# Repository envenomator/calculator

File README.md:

# Barebones AVR m328p based programmer's calculator

I was in need of a no-frills, programmer's calculator, not satisfied with the SwissMicros DM16L clone (which uses RPN), I decided to design my own.
This version powers from a USB micro cable, uses the waveshare 2inch 320x240 color display. Complete insanity, but I like it a lot.

The display is mounted to the PCB using two 2mm plastic screws, using a 3d printed shim as standoff.

The calculator with it's back plate glued on, programming port accessible.

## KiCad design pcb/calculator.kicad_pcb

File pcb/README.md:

# Barebones AVR m328p based programmer's calculator

I was in need of a no-frills, programmer's calculator, not satisfied with the SwissMicros DM16L clone (which uses RPN), I decided to design my own.
This version powers from a USB micro cable, uses the waveshare 2inch 320x240 color display. Complete insanity, but I like it a lot.
Code will follow after the PCBs return from the fab.

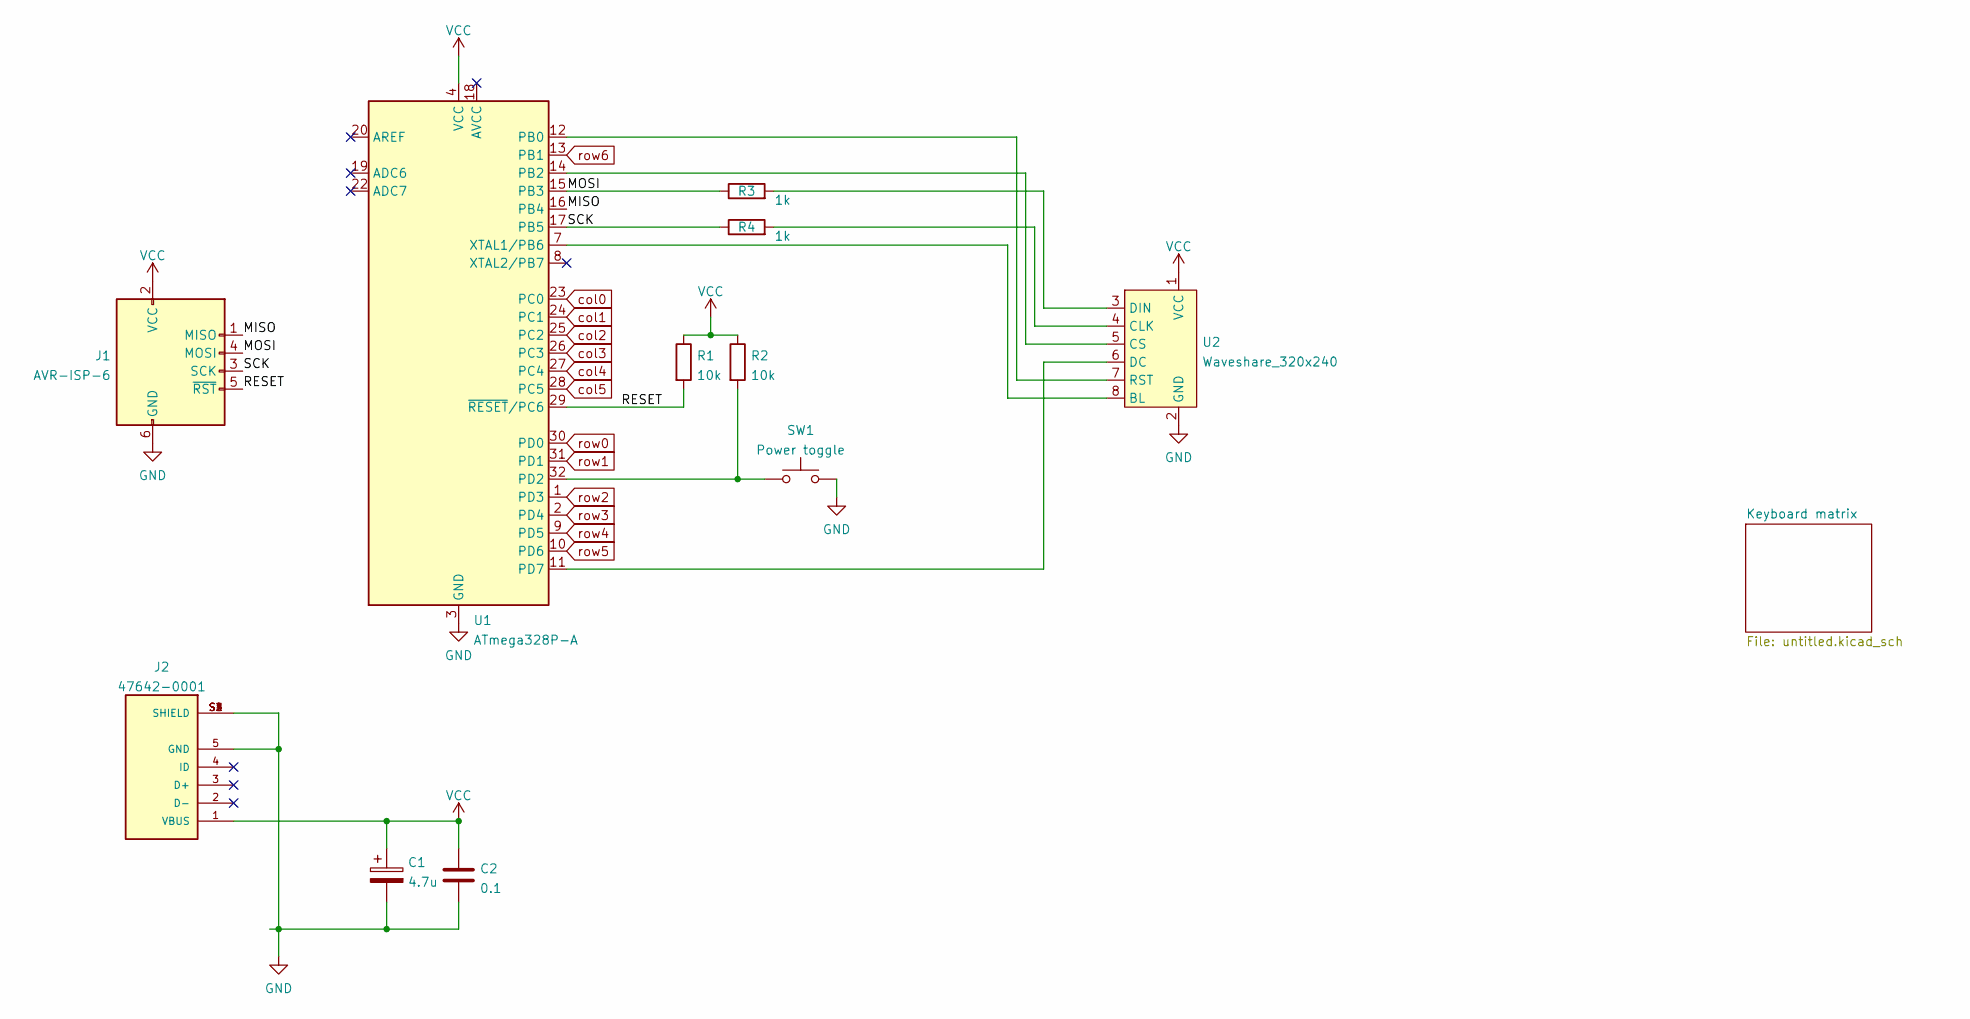
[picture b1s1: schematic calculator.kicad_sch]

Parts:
C1: 4.7u; C_0805_2012Metric_Pad1.18x1.45mm_HandSolder
C2: 0.1; C_0805_2012Metric_Pad1.18x1.45mm_HandSolder
J1: AVR-ISP-6; PinHeader_2x03_P2.54mm_Vertical
J2: 47642-0001; MOLEX_47642-0001
R1, R2: 10k; R_0805_2012Metric_Pad1.20x1.40mm_HandSolder
R3, R4: 1k; R_0805_2012Metric_Pad1.20x1.40mm_HandSolder
SW1: Power toggle; SW_PUSH_6mm
U1: ATmega328P-A; TQFP-32_7x7mm_P0.8mm
U2: Waveshare_320x240

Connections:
/MISO: J1.1 (MISO), U1.16 (PB4)
/MOSI: J1.4 (MOSI), R3.1, U1.15 (PB3)
/RESET: J1.5 (~RST), R1.2, U1.29 (~RESET/PC6)
/SCK: J1.3 (SCK), R4.1, U1.17 (PB5)
GND: C1.2, C2.2, J1.6 (GND), J2.5 (GND), J2.S1 (SHIELD), J2.S2 (SHIELD), J2.S3 (SHIELD), J2.S4 (SHIELD), SW1.2, U1.3 (GND), U1.5 (GND), U1.21 (GND), U2.2 (GND)
unnamed: R2.2, SW1.1, U1.32 (PD2)
unnamed: R3.2, U2.3 (DIN)
unnamed: R4.2, U2.4 (CLK)
unnamed: U1.7 (XTAL1/PB6), U2.8 (BL)
unnamed: U1.11 (PD7), U2.6 (DC)
unnamed: U1.12 (PB0), U2.7 (RST)
unnamed: U1.14 (PB2), U2.5 (CS)
VCC: C1.1, C2.1, J1.2 (VCC), J2.1 (VBUS), R1.1, R2.1, U1.4 (VCC), U1.6 (VCC), U2.1 (VCC)
col0: U1.23 (PC0); also elsewhere on the board
col1: U1.24 (PC1); also elsewhere on the board
col2: U1.25 (PC2); also elsewhere on the board
col3: U1.26 (PC3); also elsewhere on the board
col4: U1.27 (PC4); also elsewhere on the board
col5: U1.28 (PC5); also elsewhere on the board
row0: U1.30 (PD0); also elsewhere on the board
row1: U1.31 (PD1); also elsewhere on the board
row2: U1.1 (PD3); also elsewhere on the board
row3: U1.2 (PD4); also elsewhere on the board
row4: U1.9 (PD5); also elsewhere on the board
row5: U1.10 (PD6); also elsewhere on the board
row6: U1.13 (PB1); also elsewhere on the board

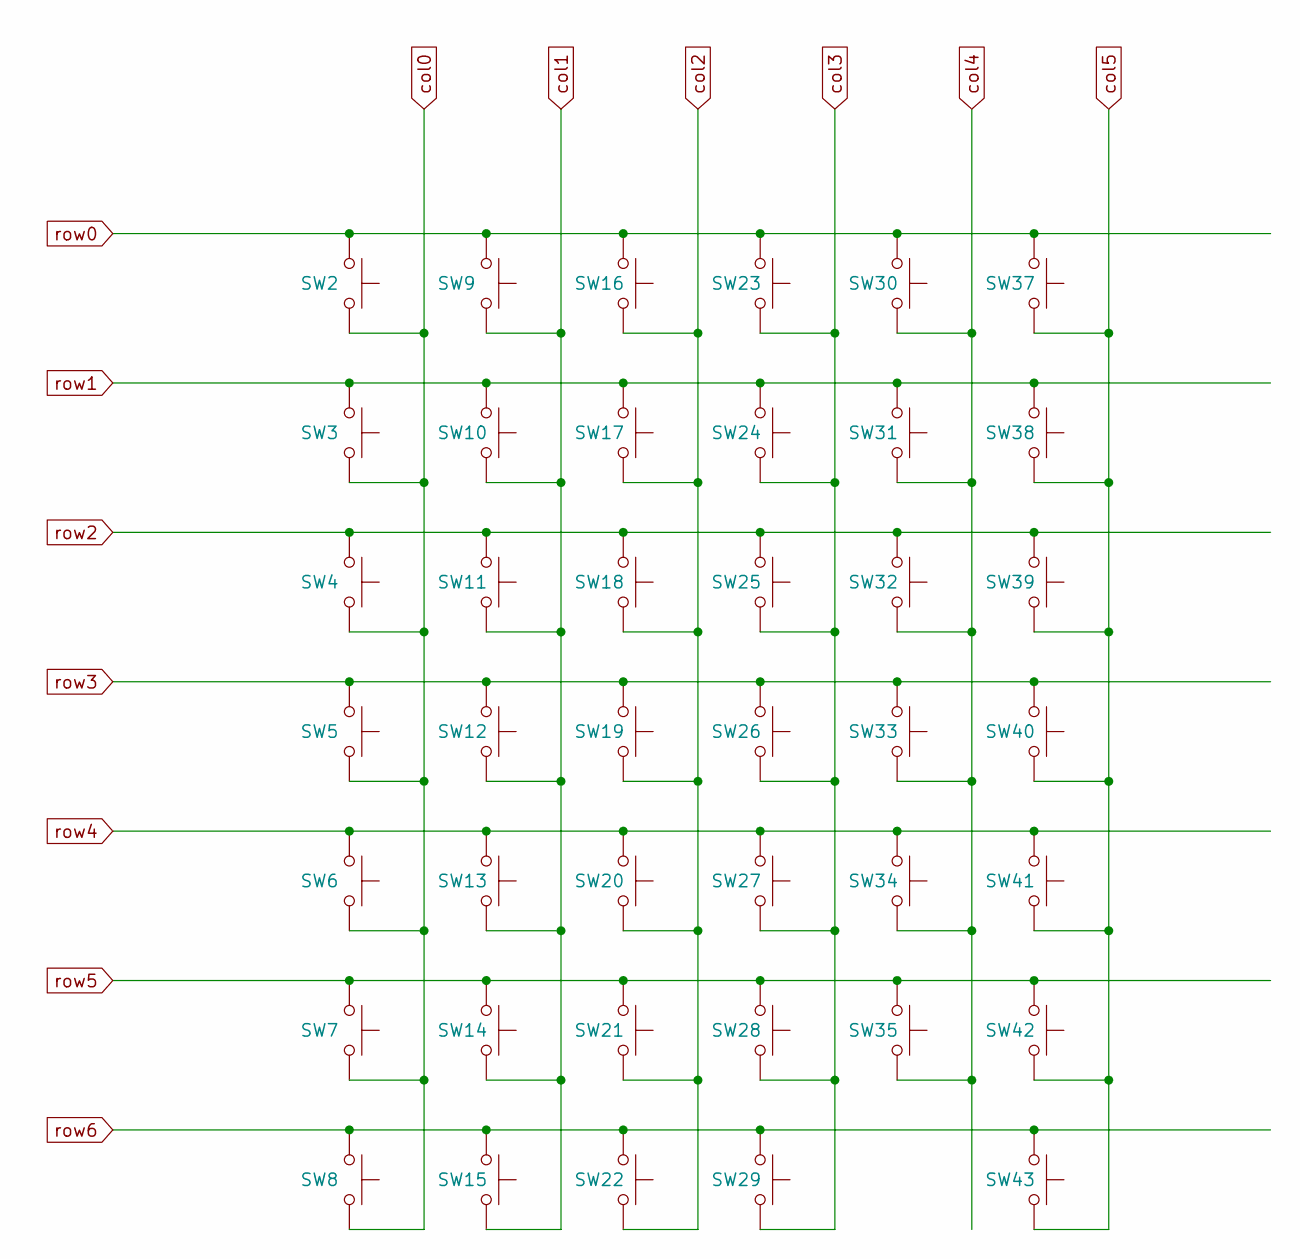
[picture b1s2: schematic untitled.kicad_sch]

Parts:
SW2: HEX; SW_PUSH_6mm
SW3, SW4, SW5, SW6, SW7, SW8, SW9, SW10, SW11, SW12, SW13, SW14, SW15, SW16, SW17, SW18, SW19, SW20, SW21, SW22, SW23, SW24, SW25, SW26, SW27, SW28, SW29, SW30, SW31, SW32, SW33, SW34, SW35, SW37, SW38, SW39, SW40, SW41, SW42, SW43: SW_Push; SW_PUSH_6mm

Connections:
col0: SW2.2, SW3.2, SW4.2, SW5.2, SW6.2, SW7.2, SW8.2; also elsewhere on the board
col1: SW9.2, SW10.2, SW11.2, SW12.2, SW13.2, SW14.2, SW15.2; also elsewhere on the board
col2: SW16.2, SW17.2, SW18.2, SW19.2, SW20.2, SW21.2, SW22.2; also elsewhere on the board
col3: SW23.2, SW24.2, SW25.2, SW26.2, SW27.2, SW28.2, SW29.2; also elsewhere on the board
col4: SW30.2, SW31.2, SW32.2, SW33.2, SW34.2, SW35.2; also elsewhere on the board
col5: SW37.2, SW38.2, SW39.2, SW40.2, SW41.2, SW42.2, SW43.2; also elsewhere on the board
row0: SW2.1, SW9.1, SW16.1, SW23.1, SW30.1, SW37.1; also elsewhere on the board
row1: SW3.1, SW10.1, SW17.1, SW24.1, SW31.1, SW38.1; also elsewhere on the board
row2: SW4.1, SW11.1, SW18.1, SW25.1, SW32.1, SW39.1; also elsewhere on the board
row3: SW5.1, SW12.1, SW19.1, SW26.1, SW33.1, SW40.1; also elsewhere on the board
row4: SW6.1, SW13.1, SW20.1, SW27.1, SW34.1, SW41.1; also elsewhere on the board
row5: SW7.1, SW14.1, SW21.1, SW28.1, SW35.1, SW42.1; also elsewhere on the board
row6: SW8.1, SW15.1, SW22.1, SW29.1, SW43.1; also elsewhere on the board

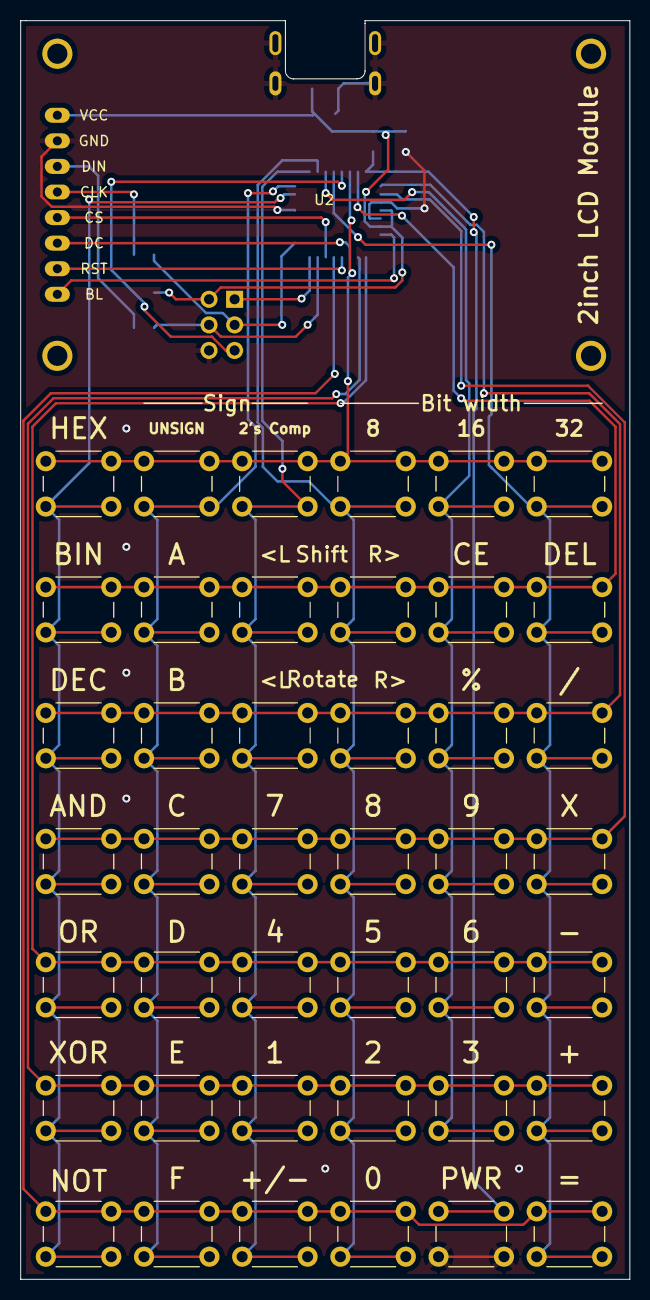
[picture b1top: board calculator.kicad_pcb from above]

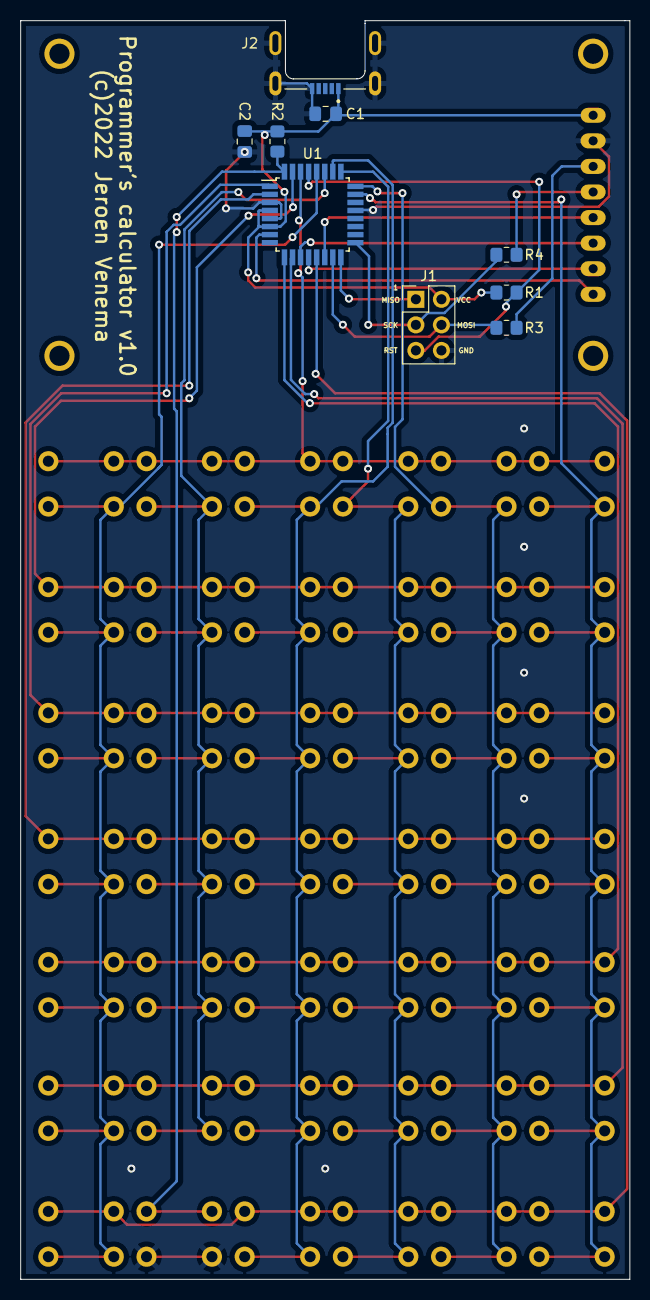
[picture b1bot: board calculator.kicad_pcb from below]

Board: 2 copper layers, 60.5 x 125.0 mm, 52 parts (9 on the bottom side), 26 nets.

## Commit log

2022-04-10 Base displayObject created
2022-04-10 Derived screen object classes done
2022-04-10 Inheritance status complete
2022-04-10 Clear bug fixed
2022-04-10 Operators working
2022-04-10 Previous result taken into consideration as input
2022-04-10 NOT calculates previous result
2022-04-10 Result kept after bit change
2022-04-10 Cleanup
2022-04-10 README
2022-04-11 Added isNegative() in status
2022-04-11 inputbox handlekey accepts sign maximums
2022-04-11 16/32bit signed mostly work, deletekey works correct
2022-04-11 Basic overflow functions
2022-04-12 Removed incorrect overflow code
2022-04-12 Flags working for C/N/O
2022-04-12 Max negative value entry now working
2022-04-12 pre-destruct
2022-04-15 Signed numbers fully working
2022-05-21 automatic font resize on display length
2022-05-21 nibble coloring partway done
2022-05-21 automatic font resize complete
2022-05-22 Colorscheme change to altcolors
2022-05-22 Removed old display32bit method
2022-05-22 7/8 pt fonts added, 8pt used for fontsize 1
2022-05-22 Status message cleanup
2022-05-22 Status message last cleanup
2022-05-22 Hex 16bit unsigned default startup
2022-05-22 60s shutdown timerafter each keypress
2024-05-09 Add files via upload
    Shim to lower the LCD to the underlying PCB
2024-05-10 Added photos

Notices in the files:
pcb/calculator.kicad_pcb:
(c)2022 Jeroen Venema
